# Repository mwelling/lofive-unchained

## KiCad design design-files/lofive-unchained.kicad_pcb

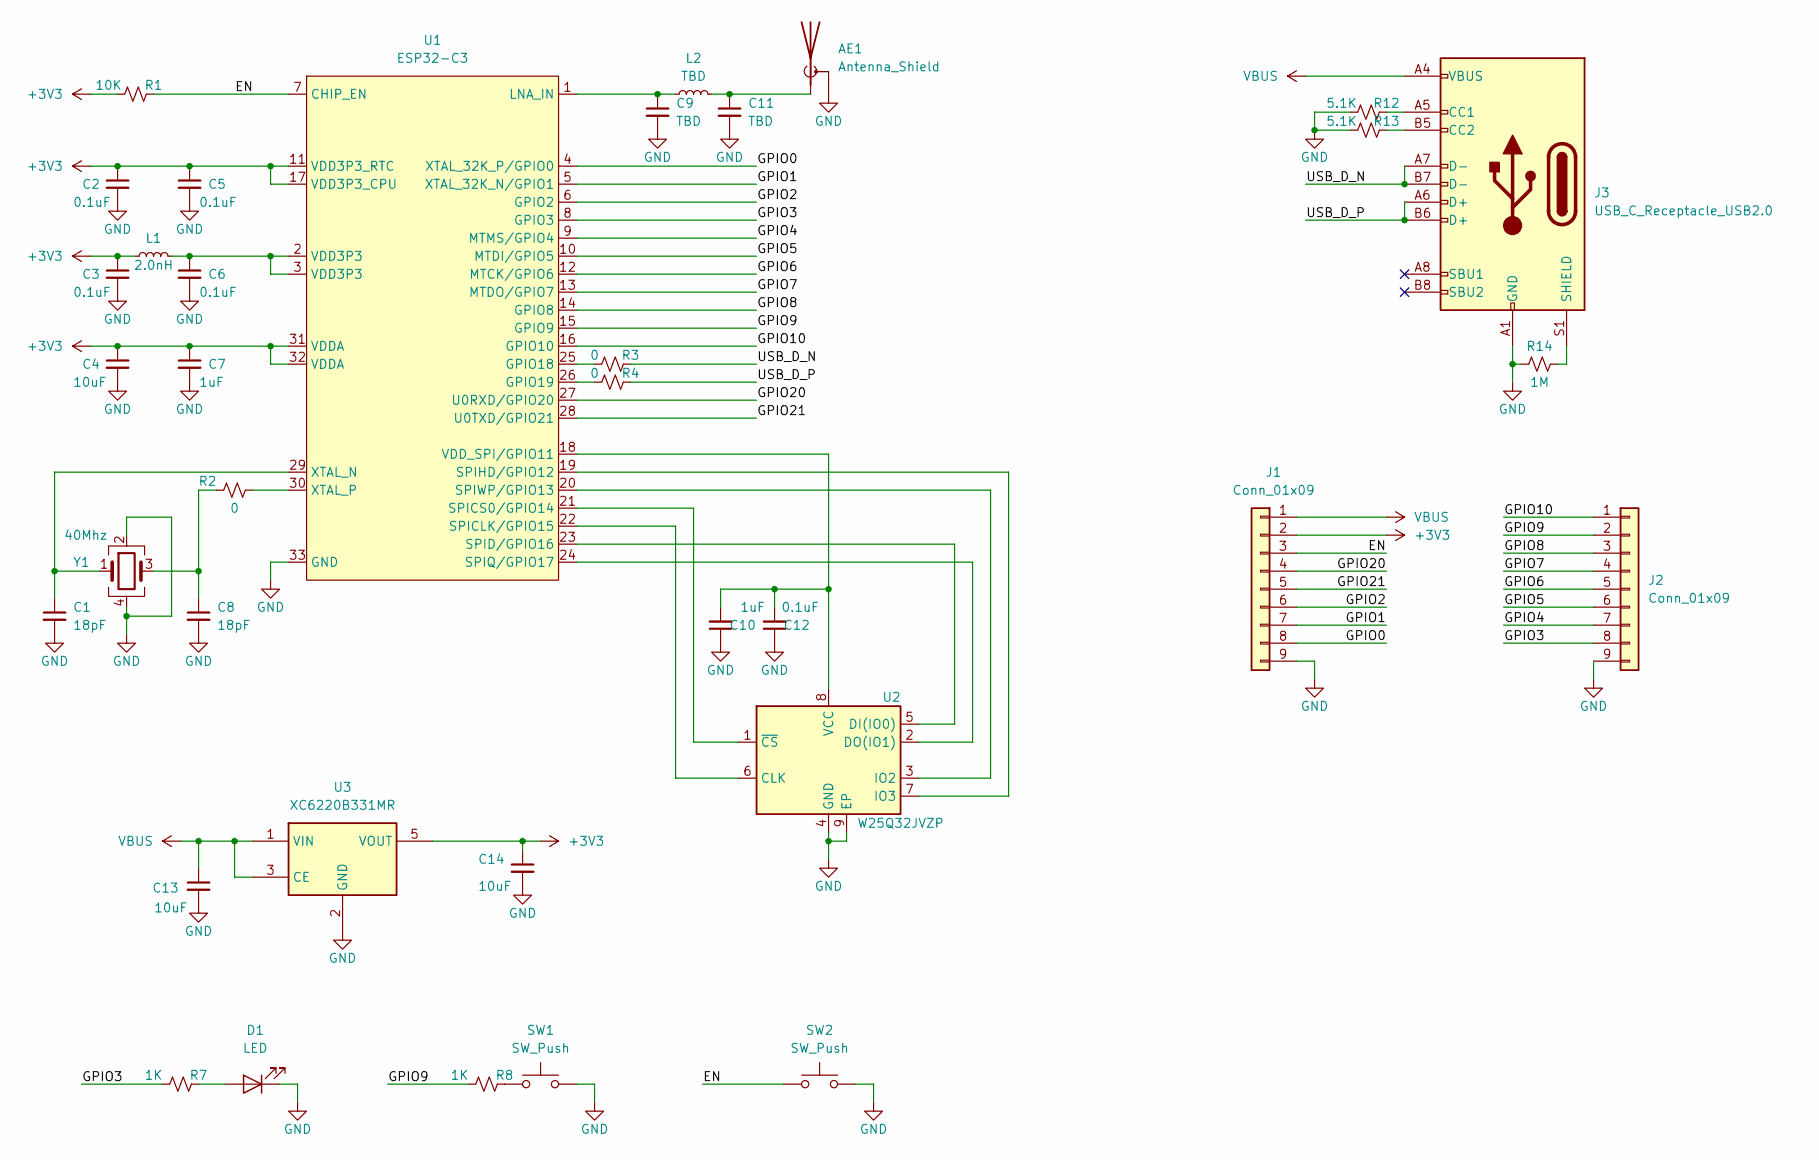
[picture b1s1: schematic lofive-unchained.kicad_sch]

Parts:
AE1: Antenna_Shield; Texas_SWRA117D_2.4GHz_Left
C1, C8: 18pF; C_0402_1005Metric
C2, C3, C5, C6, C12: 0.1uF; C_0402_1005Metric
C4, C13, C14: 10uF; C_0603_1608Metric
C7, C10: 1uF; C_0402_1005Metric
C9, C11: TBD; C_0402_1005Metric
D1: LED; LED_0603_1608Metric
J1, J2: Conn_01x09; PinHeader_1x09_P2.54mm_Vertical
J3: USB_C_Receptacle_USB2.0; USB_C_Receptacle_HRO_TYPE-C-31-M-12
L1: 2.0nH; L_0402_1005Metric
L2: TBD; L_0402_1005Metric
R1: 10K; R_0402_1005Metric
R2, R3, R4: 0; R_0402_1005Metric
R7, R8: 1K; R_0402_1005Metric
R12, R13: 5.1K; R_0402_1005Metric
R14: 1M; R_0402_1005Metric
SW1, SW2: SW_Push; SW_Push_1P1T_NO_CK_KMR2
U1: ESP32-C3; QFN-32-1EP_5x5mm_P0.5mm_EP3.6x3.6mm
U2: W25Q32JVZP; WSON-8-1EP_6x5mm_P1.27mm_EP3.4x4.3mm
U3: XC6220B331MR; SOT-23-5
Y1: 40Mhz; Crystal_SMD_2520-4Pin_2.5x2.0mm

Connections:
+3V3: C2.1, C3.1, C4.1, C5.1, C7.1, C14.1, J1.2, L1.1, R1.1, U1.11 (VDD3P3_RTC), U1.17 (VDD3P3_CPU), U1.31 (VDDA), U1.32 (VDDA), U3.5 (VOUT)
/EN: J1.3, R1.2, SW2.1, U1.7 (CHIP_EN)
/GPIO0: J1.8, U1.4 (XTAL_32K_P/GPIO0)
/GPIO1: J1.7, U1.5 (XTAL_32K_N/GPIO1)
/GPIO2: J1.6, U1.6 (GPIO2)
/GPIO3: J2.8, R7.1, U1.8 (GPIO3)
/GPIO4: J2.7, U1.9 (MTMS/GPIO4)
/GPIO5: J2.6, U1.10 (MTDI/GPIO5)
/GPIO6: J2.5, U1.12 (MTCK/GPIO6)
/GPIO7: J2.4, U1.13 (MTDO/GPIO7)
/GPIO8: J2.3, U1.14 (GPIO8)
/GPIO9: J2.2, R8.1, U1.15 (GPIO9)
/GPIO10: J2.1, U1.16 (GPIO10)
/GPIO20: J1.4, U1.27 (U0RXD/GPIO20)
/GPIO21: J1.5, U1.28 (U0TXD/GPIO21)
/USB_D_N: J3.A7 (D-), J3.B7 (D-), R3.2
/USB_D_P: J3.A6 (D+), J3.B6 (D+), R4.2
GND: AE1.2 (Shield), C1.2, C2.2, C3.2, C4.2, C5.2, C6.2, C7.2, C8.2, C9.2, C10.1, C11.2, C12.1, C13.2, C14.2, D1.1 (K), J1.9, J2.9, J3.A1 (GND), J3.A12 (GND), J3.B1 (GND), J3.B12 (GND), R12.1, R13.1, R14.1, SW1.2, SW2.2, U1.33 (GND), U2.4 (GND), U2.9 (EP), U3.2 (GND), Y1.2, Y1.4
unnamed: AE1.1 (A), C11.1, L2.2
unnamed: C6.1, L1.2, U1.2 (VDD3P3), U1.3 (VDD3P3)
unnamed: C8.1, R2.1, Y1.3
unnamed: D1.2 (A), R7.2
unnamed: J3.A5 (CC1), R12.2
unnamed: J3.B5 (CC2), R13.2
unnamed: J3.S1 (SHIELD), R14.2
unnamed: R8.2, SW1.1
unnamed: R3.1, U1.25 (GPIO18)
unnamed: R4.1, U1.26 (GPIO19)
unnamed: C9.1, L2.1, U1.1 (LNA_IN)
unnamed: U1.22 (SPICLK/GPIO15), U2.6 (CLK)
unnamed: U1.21 (SPICS0/GPIO14), U2.1 (~CS)
unnamed: U1.23 (SPID/GPIO16), U2.5 (DI(IO0))
unnamed: U1.19 (SPIHD/GPIO12), U2.7 (IO3)
unnamed: U1.24 (SPIQ/GPIO17), U2.2 (DO(IO1))
unnamed: U1.20 (SPIWP/GPIO13), U2.3 (IO2)
unnamed: C10.2, C12.2, U1.18 (VDD_SPI/GPIO11), U2.8 (VCC)
unnamed: C1.1, U1.29 (XTAL_N), Y1.1
unnamed: R2.2, U1.30 (XTAL_P)
VBUS: C13.1, J1.1, J3.A4 (VBUS), J3.A9 (VBUS), J3.B4 (VBUS), J3.B9 (VBUS), U3.1 (VIN), U3.3 (CE)

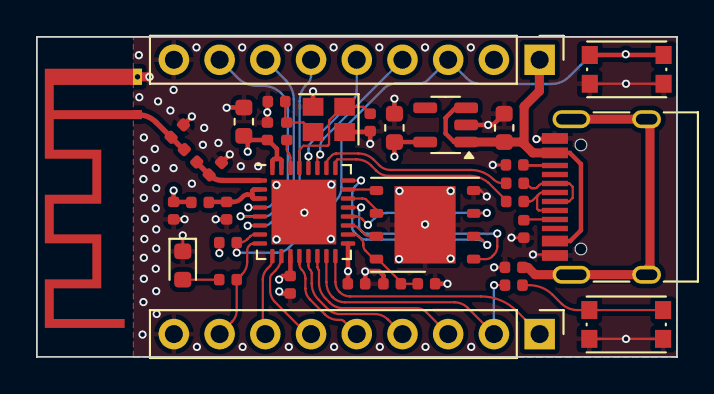
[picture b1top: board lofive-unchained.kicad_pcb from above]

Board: 4 copper layers, 35.6 x 17.8 mm, 36 parts (0 on the bottom side), 39 nets.

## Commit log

2021-12-15 Initial commit of design files
2021-12-15 Rename folder with design files
2021-12-21 Preliminary routing complete
    Need to check the RF trace and USB routing.
2021-12-21 Update minimum hole size
    Get rid of a bunch of DRC errors.
2021-12-22 Switch to HRO USB connector
    Available at LCSC.
2022-01-13 Add consummate vias and plot
2022-02-01 Post ibom and gerber zip
2024-12-01 Switch to 3.3V LDO instead of switcher
